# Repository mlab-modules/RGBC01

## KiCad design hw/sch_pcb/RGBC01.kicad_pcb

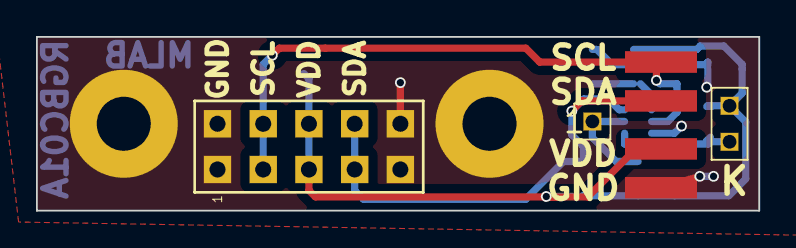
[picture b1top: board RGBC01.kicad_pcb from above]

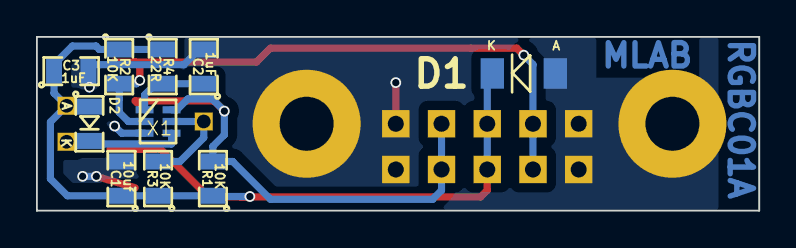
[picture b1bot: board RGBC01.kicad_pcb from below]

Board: 2 copper layers, 40.1 x 9.7 mm, 19 parts (12 on the bottom side), 7 nets.

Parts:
C1: 10uf; SMD-0805
C2, C3: 1uF; SMD-0805
D1: BZV55C-3,6V; Diode-MiniMELF_Standard
D2: LL-S170IRC-2A; LED_0805
J1: JUMP_5X2; Straight_2x05
J2: CONN1_1; Straight_1x01
J3: CONN1_2; Straight_2x01
J4, J5, J6, J7: CONN1_1; SMD_1x1
M1, M2: HOLE; MountingHole_3mm
R1, R2, R3: 10K; SMD-0805
R4: 22R; SMD-0805
X1: TCS37717; FN

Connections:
/SCL: J1.3, J1.4, J5.1, R2.2, X1.2
/SDA: J1.7, J1.8, J6.1, R1.2, X1.6
GND: C1.2, C2.2, C3.2, D1.1, J1.1, J1.2, J1.9, J1.10, J7.1, M1.1, M2.1, X1.3
unnamed: C2.1, R4.2, X1.1
unnamed: D2.2, J3.2, X1.4
unnamed: J2.1, R3.2, X1.5
VDD: C1.1, C3.1, D1.2, D2.1, J1.5, J1.6, J3.1, J4.1, R1.1, R2.1, R3.1, R4.1

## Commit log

2023-04-01 Adding force option to enable splitting in not fresh copy of Modules repository.
2023-05-28 automated commit; add github actions
2023-05-28 Update workflow files
2023-05-28 Update metadata files
2023-07-05 automated commit; rename source files to new naming convence
2023-09-16 Update status
2023-09-17 Convert project to KiCAD 7.
2023-09-17 Update actions products
2023-09-17 Update metadata.yaml
    Set title image.
